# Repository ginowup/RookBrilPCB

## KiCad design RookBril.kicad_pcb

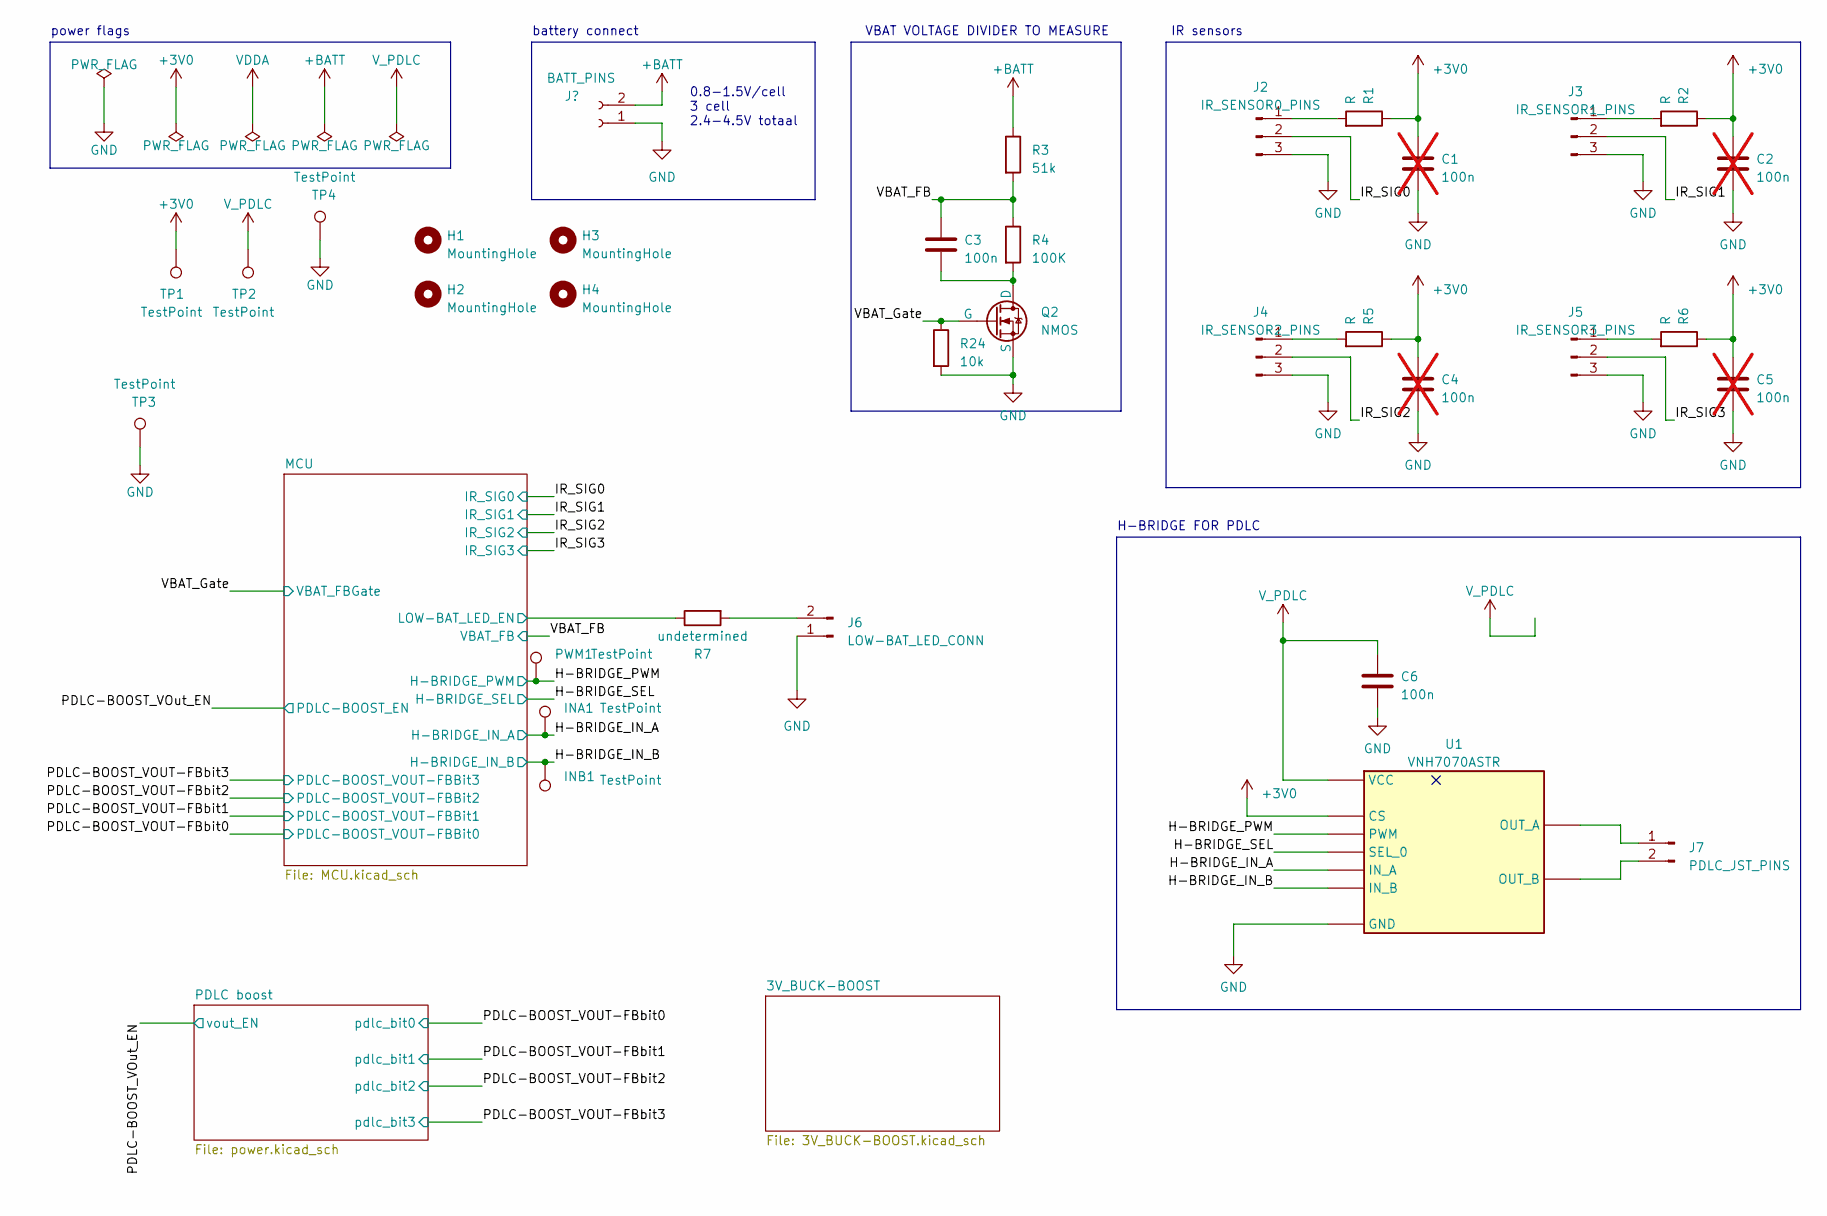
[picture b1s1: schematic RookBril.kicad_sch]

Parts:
C1, C2, C4, C5: 100n; C_0805_2012Metric_Pad1.18x1.45mm_HandSolder; not fitted
C3, C6: 100n; C_0805_2012Metric_Pad1.18x1.45mm_HandSolder
H1, H2, H3, H4: MountingHole; MountingHole_3mm
INA1: TestPoint; TestPoint_Pad_D1.0mm
INB1: TestPoint; TestPoint_Pad_D1.0mm
J1: BATT_PINS; PinHeader_1x02_P2.54mm_Vertical
J2: IR_SENSOR0_PINS; PinHeader_1x03_P2.54mm_Vertical
J3: IR_SENSOR1_PINS; PinHeader_1x03_P2.54mm_Vertical
J4: IR_SENSOR2_PINS; PinHeader_1x03_P2.54mm_Vertical
J5: IR_SENSOR3_PINS; PinHeader_1x03_P2.54mm_Vertical
J6: LOW-BAT_LED_CONN; PinHeader_1x02_P2.54mm_Vertical
J7: PDLC_JST_PINS; PinHeader_1x02_P2.54mm_Vertical
PWM1: TestPoint; TestPoint_Pad_D1.0mm
Q2: NMOS; SOT-23
R1, R2, R5, R6: R; R_0805_2012Metric_Pad1.20x1.40mm_HandSolder
R3: 51k; R_0805_2012Metric_Pad1.20x1.40mm_HandSolder
R4: 100K; R_0805_2012Metric_Pad1.20x1.40mm_HandSolder
R7: undetermined; R_0805_2012Metric_Pad1.20x1.40mm_HandSolder
R24: 10k; R_0805_2012Metric_Pad1.20x1.40mm_HandSolder
TP1, TP2, TP4: TestPoint; TestPoint_Plated_Hole_D2.0mm
TP3: TestPoint; exposedPad5x10
U1: VNH7070ASTR; SOIC127P600X175-16N; Manufacturer_Part_Number VNH7070ASTR; Mouser Part Number 511-VNH7070ASTR

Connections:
+3V0: C1.1, C2.1, C4.1, C5.1, R1.1, R2.1, R5.1, R6.1, TP1.1, U1.13 (CS); also elsewhere on the board
+BATT: J1.2, R3.1; also elsewhere on the board
/H-BRIDGE_IN_A: INA1.1, U1.3 (IN_A); also elsewhere on the board
/H-BRIDGE_IN_B: INB1.1, U1.6 (IN_B); also elsewhere on the board
/H-BRIDGE_PWM: PWM1.1, U1.11 (PWM); also elsewhere on the board
/H-BRIDGE_SEL: U1.14 (SEL_0); also elsewhere on the board
/IR_SIG0: J2.2; also elsewhere on the board
/IR_SIG1: J3.2; also elsewhere on the board
/IR_SIG2: J4.2; also elsewhere on the board
/IR_SIG3: J5.2; also elsewhere on the board
/MCU/LOW-BAT_LED_EN: R7.1; also elsewhere on the board
/VBAT_FB: C3.1, R3.2, R4.1; also elsewhere on the board
GND: C1.2, C2.2, C4.2, C5.2, C6.2, J1.1, J2.3, J3.3, J4.3, J5.3, J6.1, Q2.3 (S), R24.2, TP3.1, TP4.1, U1.1 (GND), U1.8 (GND), U1.9 (GND), U1.16 (GND); also elsewhere on the board
unnamed: J2.1, R1.2
unnamed: J3.1, R2.2
unnamed: J4.1, R5.2
unnamed: J5.1, R6.2
unnamed: J6.2, R7.2
unnamed: J7.1, U1.2 (OUT_A), U1.15 (OUT_A)
unnamed: J7.2, U1.7 (OUT_B), U1.10 (OUT_B)
VCC: C6.1, TP2.1, U1.4 (VCC), U1.5 (VCC), U1.12 (VCC); also elsewhere on the board

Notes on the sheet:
0.8-1.5V/cell 3 cell 2.4-4.5V totaal
VBAT VOLTAGE DIVIDER TO MEASURE
battery connect
IR sensors
H-BRIDGE FOR PDLC
power flags

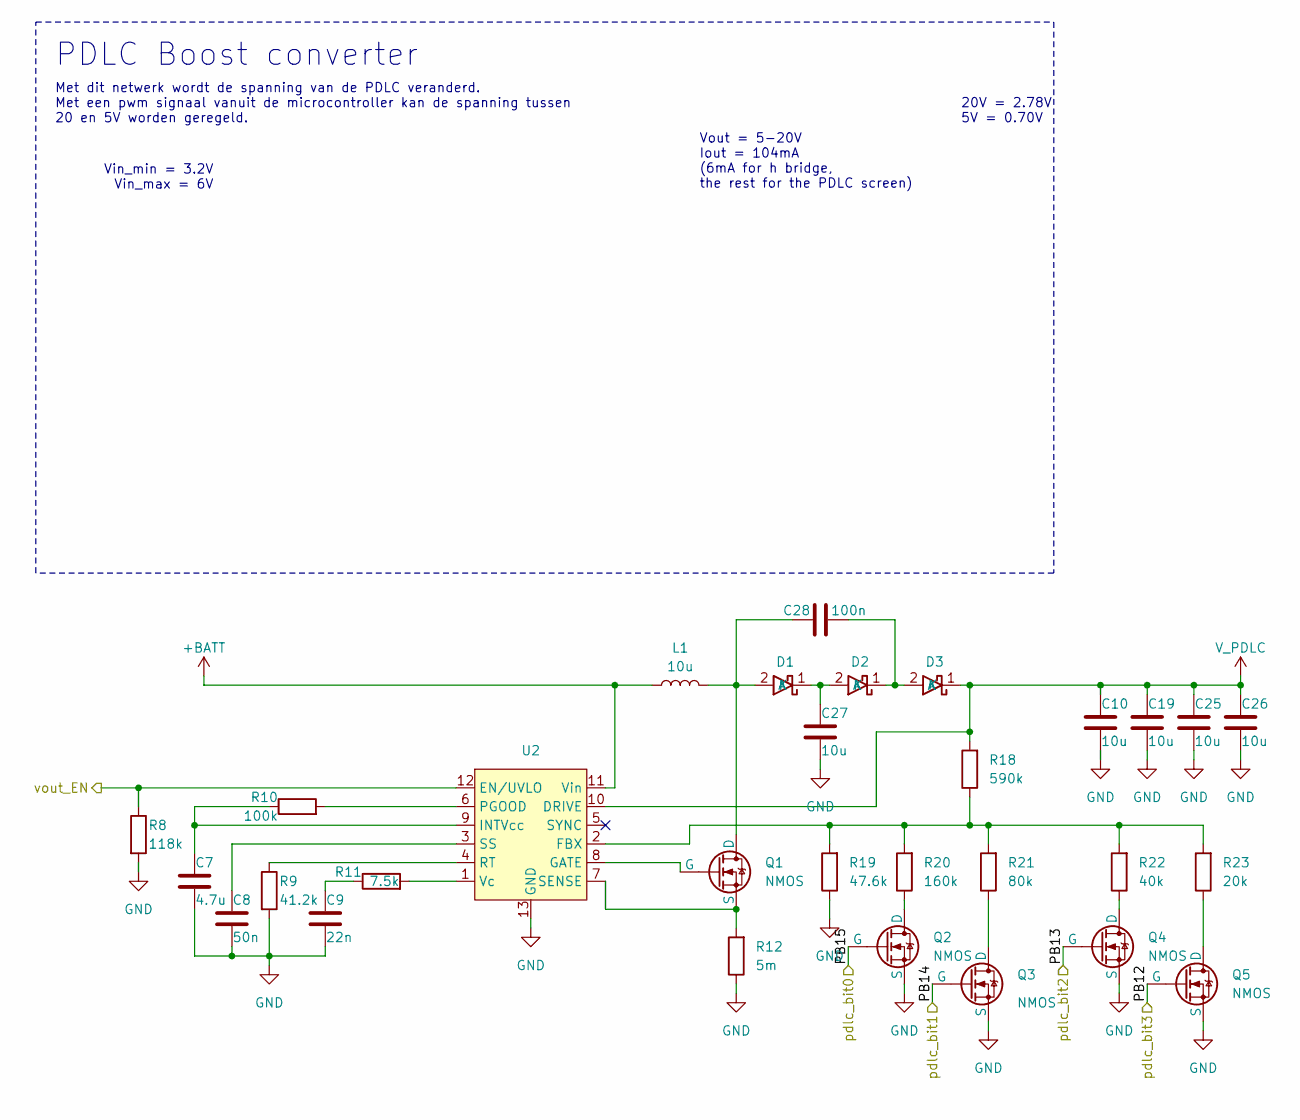
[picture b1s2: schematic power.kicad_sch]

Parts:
C7: 4.7u; C_0805_2012Metric_Pad1.18x1.45mm_HandSolder
C8: 50n; C_0805_2012Metric_Pad1.18x1.45mm_HandSolder
C9: 22n; C_0805_2012Metric_Pad1.18x1.45mm_HandSolder
C10, C19, C25, C26, C27: 10u; C_0805_2012Metric_Pad1.18x1.45mm_HandSolder
C28: 100n; C_0805_2012Metric_Pad1.18x1.45mm_HandSolder
D1, D2, D3: D_SOD-123F
L1: 10u; MRS8030T100
Q1, Q2, Q3, Q4, Q5: NMOS; SOT-23
R8: 118k; R_0805_2012Metric_Pad1.20x1.40mm_HandSolder
R9: 41.2k; R_0805_2012Metric_Pad1.20x1.40mm_HandSolder
R10: 100k; R_0805_2012Metric_Pad1.20x1.40mm_HandSolder
R11: 7.5k; R_0805_2012Metric_Pad1.20x1.40mm_HandSolder
R12: 5m; R_2010_5025Metric_Pad1.40x2.65mm_HandSolder
R18: 590k; R_0805_2012Metric_Pad1.20x1.40mm_HandSolder
R19: 47.6k; R_0805_2012Metric_Pad1.20x1.40mm_HandSolder
R20: 160k; R_0805_2012Metric_Pad1.20x1.40mm_HandSolder
R21: 80k; R_0805_2012Metric_Pad1.20x1.40mm_HandSolder
R22: 40k; R_0805_2012Metric_Pad1.20x1.40mm_HandSolder
R23: 20k; R_0805_2012Metric_Pad1.20x1.40mm_HandSolder
U2: LT3759

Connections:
+BATT: L1.1, U2.11 (Vin); also elsewhere on the board
/PDLC-BOOST_VOUT-FBbit1: Q3.2 (G); also elsewhere on the board
/PDLC-BOOST_VOUT-FBbit2: Q4.2 (G); also elsewhere on the board
/PDLC-BOOST_VOUT-FBbit3: Q5.2 (G); also elsewhere on the board
/PDLC-BOOST_VOut_EN: R8.1, U2.12 (EN/UVLO); also elsewhere on the board
GND: C7.1, C8.1, C9.1, C10.1, C19.1, C25.1, C26.1, C27.1, Q2.3 (S), Q3.3 (S), Q4.3 (S), Q5.3 (S), R8.2, R9.2, R12.1, R19.1, U2.13 (GND); also elsewhere on the board
unnamed: C9.2, R11.1
unnamed: C28.2, D1.2 (A), L1.2, Q1.1 (D)
unnamed: C27.2, D1.1 (K), D2.2 (A)
unnamed: C28.1, D2.1 (K), D3.2 (A)
unnamed: Q1.2 (G), U2.8 (GATE)
unnamed: Q1.3 (S), R12.2, U2.7 (SENSE)
unnamed: Q3.1 (D), R21.1
unnamed: Q4.1 (D), R22.1
unnamed: Q5.1 (D), R23.1
unnamed: R18.1, R19.2, R20.2, R21.2, R22.2, R23.2, U2.2 (FBX)
unnamed: C7.2, R10.1, U2.9 (INTVcc)
unnamed: R10.2, U2.6 (PGOOD)
unnamed: R9.1, U2.4 (RT)
unnamed: C8.2, U2.3 (SS)
unnamed: R11.2, U2.1 (Vc)
VCC: C10.2, C19.2, C25.2, C26.2, D3.1 (K), R18.2, U2.10 (DRIVE); also elsewhere on the board

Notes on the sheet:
Vout = 5-20V Iout = 104mA (6mA for h bridge, the rest for the PDLC screen)
Vin_min = 3.2V Vin_max = 6V
20V = 2.78V 5V = 0.70V
PDLC Boost converter
Met dit netwerk wordt de spanning van de PDLC veranderd. Met een pwm signaal vanuit de microcontroller kan de spanning tussen 20 en 5V worden geregeld.

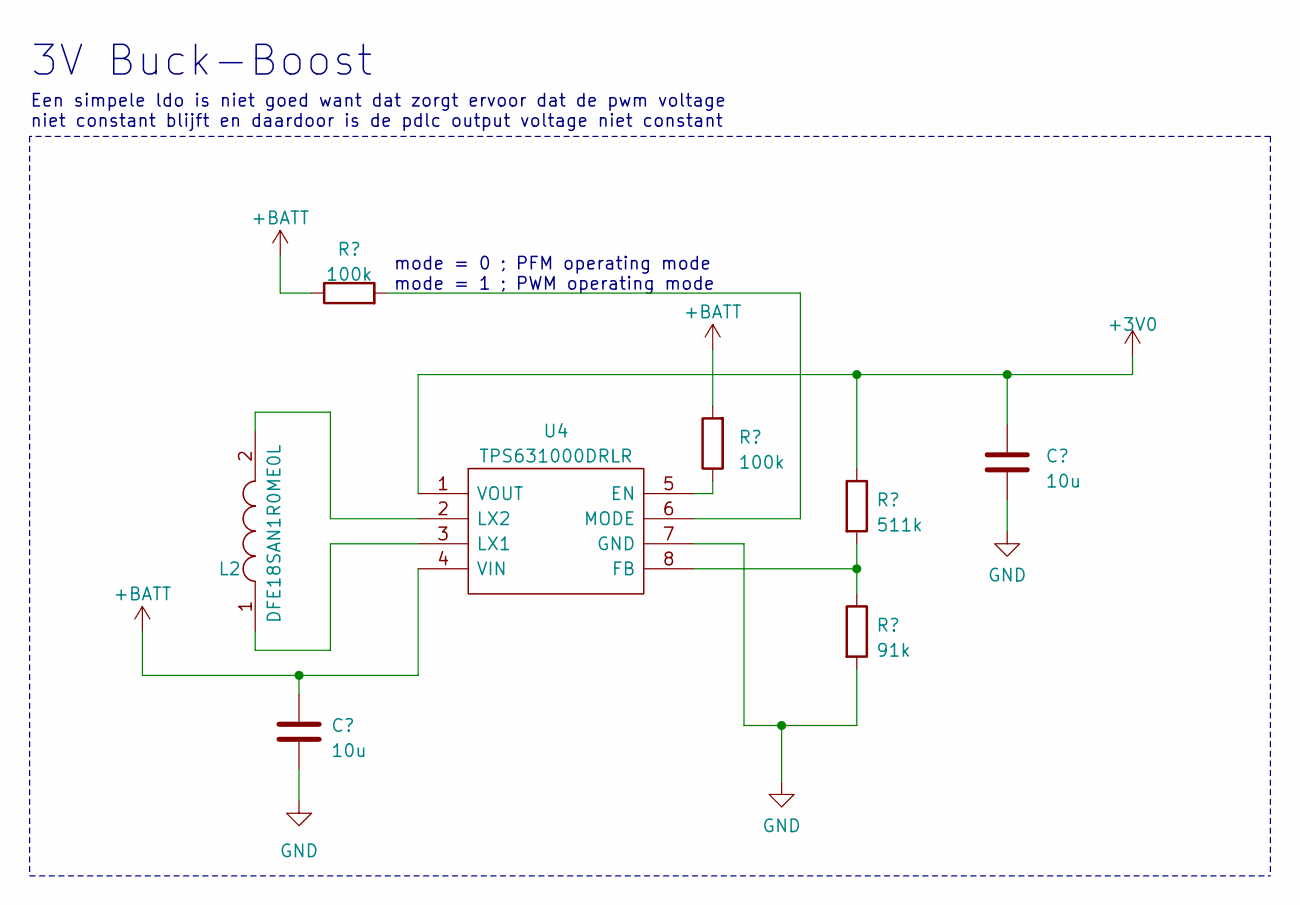
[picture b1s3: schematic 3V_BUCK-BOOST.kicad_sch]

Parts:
C22, C23: 10u; C_0805_2012Metric_Pad1.18x1.45mm_HandSolder
L2: DFE18SAN1R0ME0L; Mouser Part Number 81-DFE18SAN1R0ME0L
R14, R15: 100k; R_0805_2012Metric_Pad1.20x1.40mm_HandSolder
R16: 511k; R_0805_2012Metric_Pad1.20x1.40mm_HandSolder
R17: 91k; R_0805_2012Metric_Pad1.20x1.40mm_HandSolder
U4: TPS631000DRLR; SOTFL50P160X60-8N; Mouser Part Number 595-TPS631000DRLR

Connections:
+3V0: C22.1, R16.1, U4.1 (VOUT); also elsewhere on the board
+BATT: C23.1, R14.1, R15.2, U4.4 (VIN); also elsewhere on the board
GND: C22.2, C23.2, R17.2, U4.7 (GND); also elsewhere on the board
unnamed: R15.1, U4.5 (EN)
unnamed: R16.2, R17.1, U4.8 (FB)
unnamed: L2.1, U4.3 (LX1)
unnamed: L2.2, U4.2 (LX2)
unnamed: R14.2, U4.6 (MODE)

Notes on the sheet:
3V Buck-Boost
Een simpele ldo is niet goed want dat zorgt ervoor dat de pwm voltage niet constant blijft en daardoor is de pdlc output voltage niet constant
mode = 0 ; PFM operating mode mode = 1 ; PWM operating mode

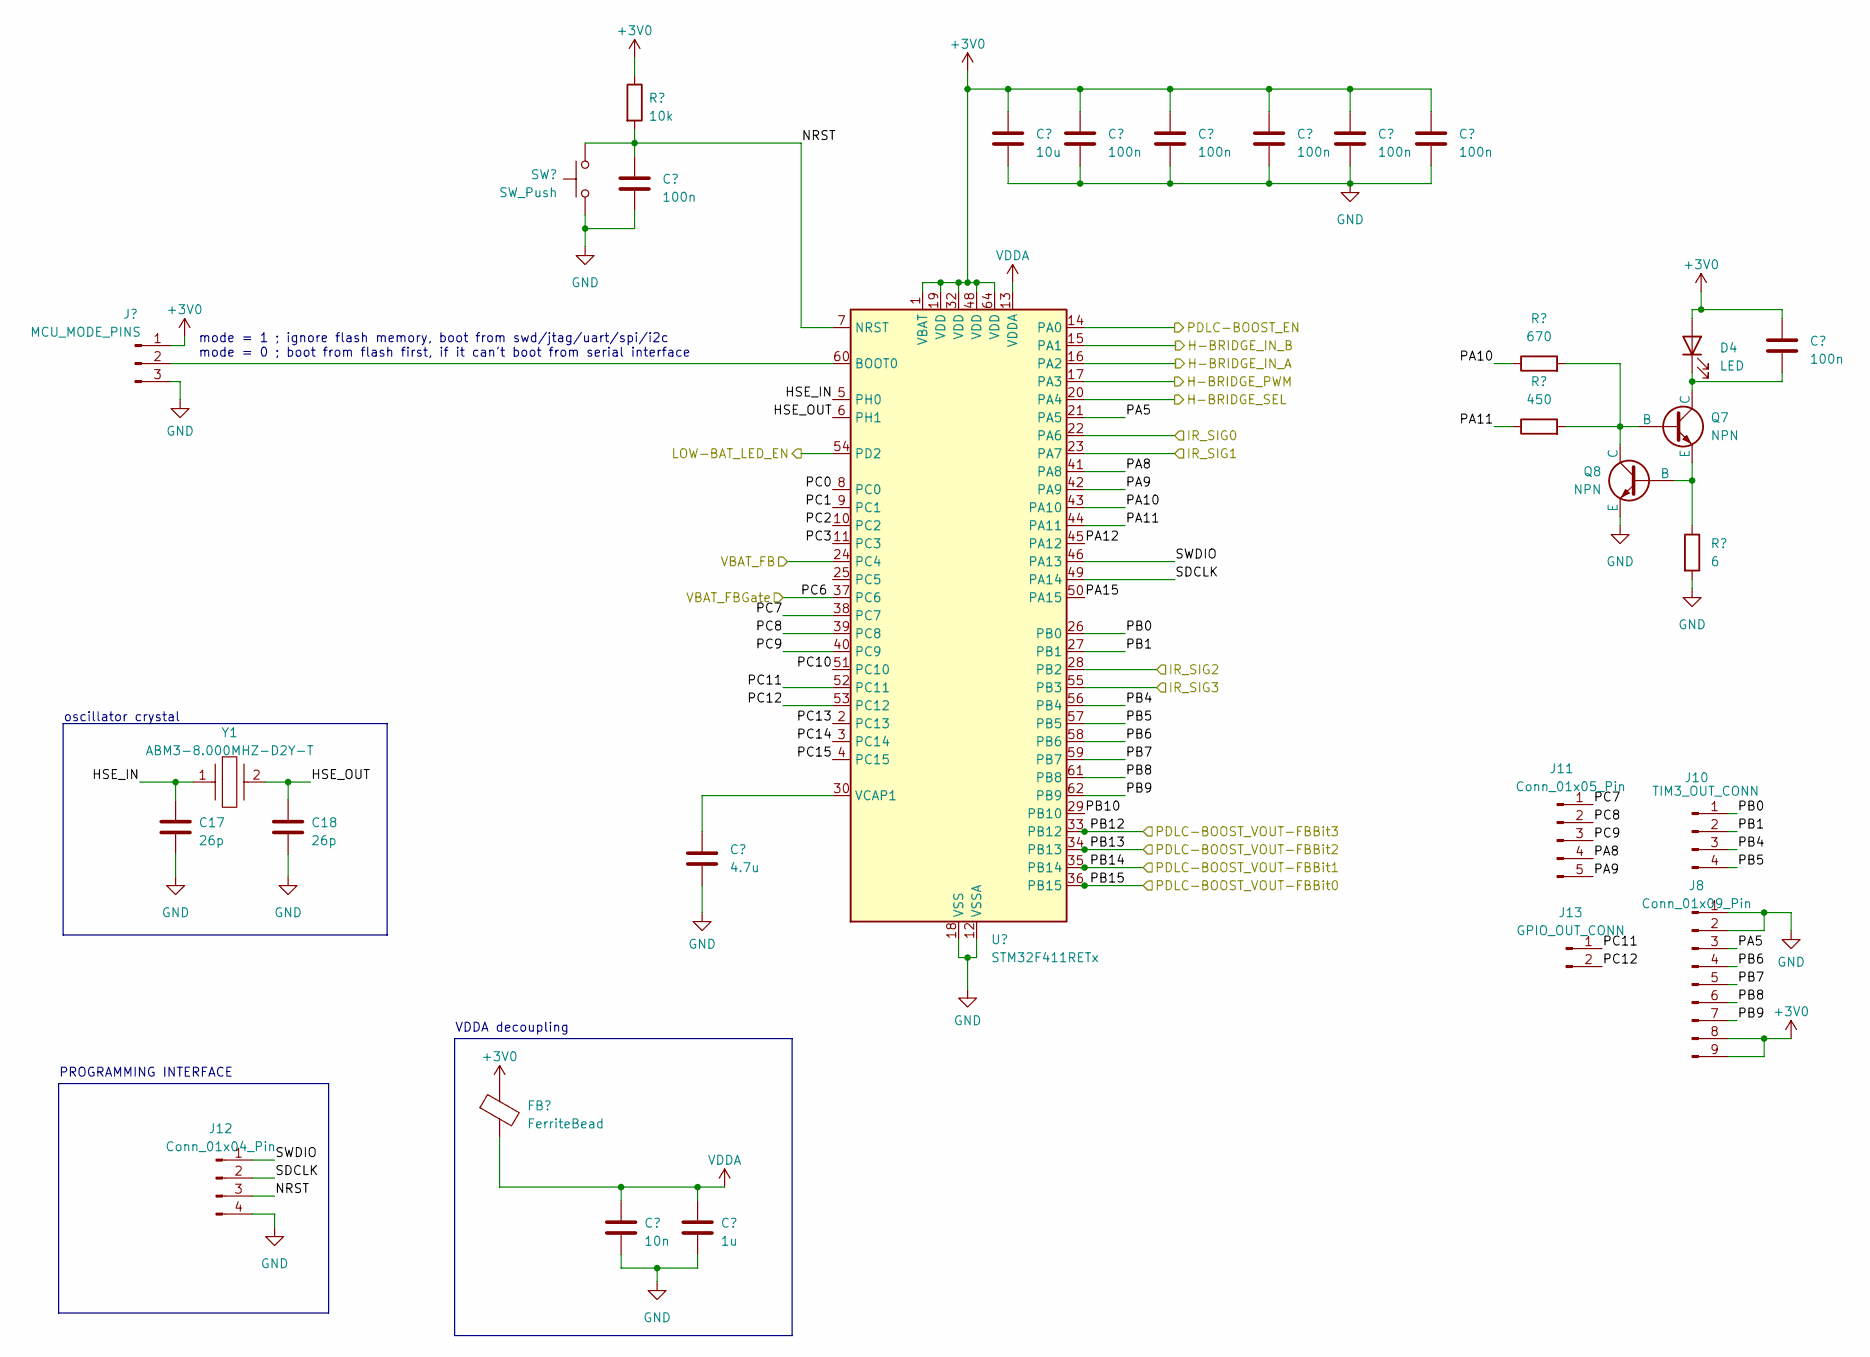
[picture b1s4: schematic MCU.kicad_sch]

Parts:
C11: 10u; C_0805_2012Metric_Pad1.18x1.45mm_HandSolder
C12, C13, C14, C15, C16, C24, C30: 100n; C_0805_2012Metric_Pad1.18x1.45mm_HandSolder
C17, C18: 26p; C_0805_2012Metric_Pad1.18x1.45mm_HandSolder
C20: 10n; C_0805_2012Metric_Pad1.18x1.45mm_HandSolder
C21: 1u; C_0805_2012Metric_Pad1.18x1.45mm_HandSolder
C29: 4.7u; C_0805_2012Metric_Pad1.18x1.45mm_HandSolder
D4: LED; IRLED
FB1: FerriteBead; L_0805_2012Metric_Pad1.15x1.40mm_HandSolder
J8: Conn_01x09_Pin; PinHeader_1x09_P2.54mm_Vertical
J9: MCU_MODE_PINS; PinHeader_1x03_P2.54mm_Vertical
J10: TIM3_OUT_CONN; PinHeader_1x04_P2.54mm_Vertical
J11: Conn_01x05_Pin; PinHeader_1x05_P2.54mm_Vertical
J12: Conn_01x04_Pin; PinHeader_1x04_P2.54mm_Vertical
J13: GPIO_OUT_CONN; PinHeader_1x02_P2.54mm_Vertical
Q7, Q8: NPN; SOT-23
R13: 10k; R_0805_2012Metric_Pad1.20x1.40mm_HandSolder
R25: 6; R_0805_2012Metric_Pad1.20x1.40mm_HandSolder
R26: 450; R_0805_2012Metric_Pad1.20x1.40mm_HandSolder
R27: 670; R_0805_2012Metric_Pad1.20x1.40mm_HandSolder
SW1: SW_Push; SW_PUSH_6mm_H5mm
U3: STM32F411RETx; LQFP-64_10x10mm_P0.5mm
Y1: ABM3-8.000MHZ-D2Y-T; ABM3; Mouser Part Number 815-ABM3-8-D2Y-T

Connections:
+3V0: C11.1, C12.1, C13.1, C14.1, C15.1, C24.1, C30.1, D4.2 (A), FB1.1, J8.8, J8.9, J9.1, R13.1, U3.1 (VBAT), U3.19 (VDD), U3.32 (VDD), U3.48 (VDD), U3.64 (VDD); also elsewhere on the board
/H-BRIDGE_IN_A: U3.16 (PA2); also elsewhere on the board
/H-BRIDGE_IN_B: U3.15 (PA1); also elsewhere on the board
/H-BRIDGE_PWM: U3.17 (PA3); also elsewhere on the board
/H-BRIDGE_SEL: U3.20 (PA4); also elsewhere on the board
/IR_SIG0: U3.22 (PA6); also elsewhere on the board
/IR_SIG1: U3.23 (PA7); also elsewhere on the board
/IR_SIG2: U3.28 (PB2); also elsewhere on the board
/IR_SIG3: U3.55 (PB3); also elsewhere on the board
/MCU/HSE_IN: C17.1, U3.5 (PH0), Y1.1
/MCU/HSE_OUT: C18.1, U3.6 (PH1), Y1.2
/MCU/LOW-BAT_LED_EN: U3.54 (PD2); also elsewhere on the board
/MCU/NRST: C16.1, J12.3, R13.2, SW1.1, U3.7 (NRST)
/MCU/PA5: J8.3, U3.21 (PA5)
/MCU/PA8: J11.4, U3.41 (PA8)
/MCU/PA9: J11.5, U3.42 (PA9)
/MCU/PA10: R27.1, U3.43 (PA10)
/MCU/PA11: R26.1, U3.44 (PA11)
/MCU/PA12: U3.45 (PA12)
/MCU/PA15: U3.50 (PA15)
/MCU/PB0: J10.1, U3.26 (PB0)
/MCU/PB1: J10.2, U3.27 (PB1)
/MCU/PB4: J10.3, U3.56 (PB4)
/MCU/PB5: J10.4, U3.57 (PB5)
/MCU/PB6: J8.4, U3.58 (PB6)
/MCU/PB7: J8.5, U3.59 (PB7)
/MCU/PB8: J8.6, U3.61 (PB8)
/MCU/PB9: J8.7, U3.62 (PB9)
/MCU/PB10: U3.29 (PB10)
/MCU/PC0: U3.8 (PC0)
/MCU/PC1: U3.9 (PC1)
/MCU/PC2: U3.10 (PC2)
/MCU/PC3: U3.11 (PC3)
/MCU/PC7: J11.1, U3.38 (PC7)
/MCU/PC8: J11.2, U3.39 (PC8)
/MCU/PC9: J11.3, U3.40 (PC9)
/MCU/PC10: U3.51 (PC10)
/MCU/PC11: J13.1, U3.52 (PC11)
/MCU/PC12: J13.2, U3.53 (PC12)
/MCU/PC13: U3.2 (PC13)
/MCU/PC14: U3.3 (PC14)
/MCU/PC15: U3.4 (PC15)
/MCU/SDCLK: J12.2, U3.49 (PA14)
/MCU/SWDIO: J12.1, U3.46 (PA13)
/PDLC-BOOST_VOUT-FBbit1: U3.35 (PB14); also elsewhere on the board
/PDLC-BOOST_VOUT-FBbit2: U3.34 (PB13); also elsewhere on the board
/PDLC-BOOST_VOUT-FBbit3: U3.33 (PB12); also elsewhere on the board
/PDLC-BOOST_VOut_EN: U3.14 (PA0); also elsewhere on the board
/VBAT_FB: U3.24 (PC4); also elsewhere on the board
GND: C11.2, C12.2, C13.2, C14.2, C15.2, C16.2, C17.2, C18.2, C20.2, C21.2, C24.2, C29.2, J8.1, J8.2, J9.3, J12.4, Q8.3 (E), R25.2, SW1.2, U3.12 (VSSA), U3.18 (VSS), U3.31 (VSS), U3.47 (VSS), U3.63 (VSS); also elsewhere on the board
unnamed: C30.2, D4.1 (K), Q7.1 (C)
unnamed: J9.2, U3.60 (BOOT0)
unnamed: Q7.2 (B), Q8.1 (C), R26.2, R27.2
unnamed: Q7.3 (E), Q8.2 (B), R25.1
unnamed: C29.1, U3.30 (VCAP1)
VDDA: C20.1, C21.1, FB1.2, U3.13 (VDDA)

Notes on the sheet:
VDDA decoupling
PROGRAMMING INTERFACE
oscillator crystal
mode = 1 ; ignore flash memory, boot from swd/jtag/uart/spi/i2c mode = 0 ; boot from flash first, if it can't boot from serial interface

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
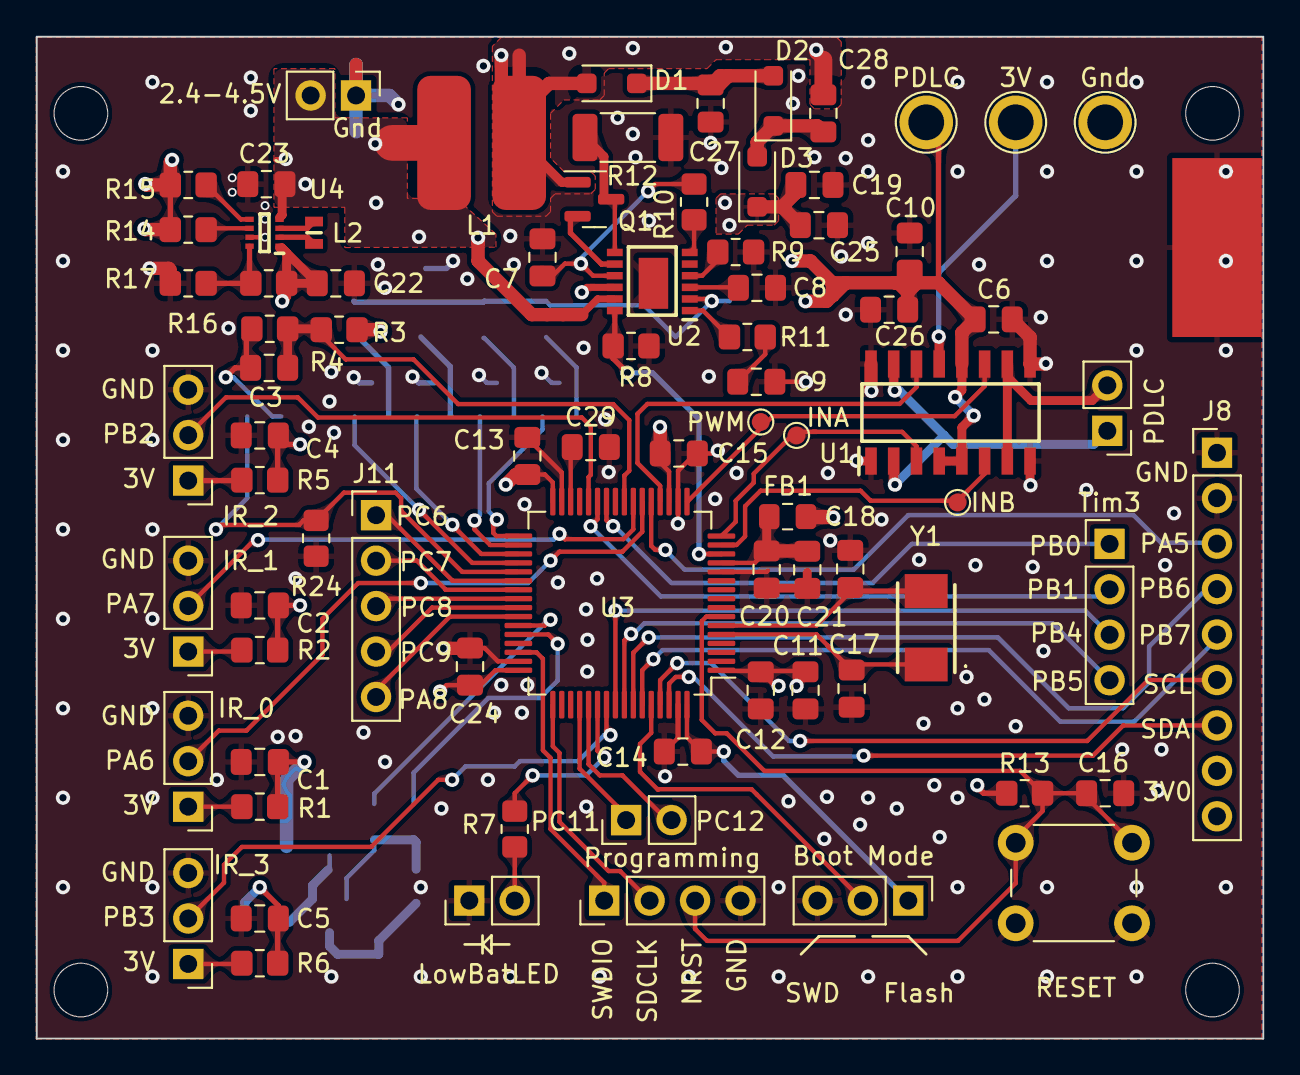
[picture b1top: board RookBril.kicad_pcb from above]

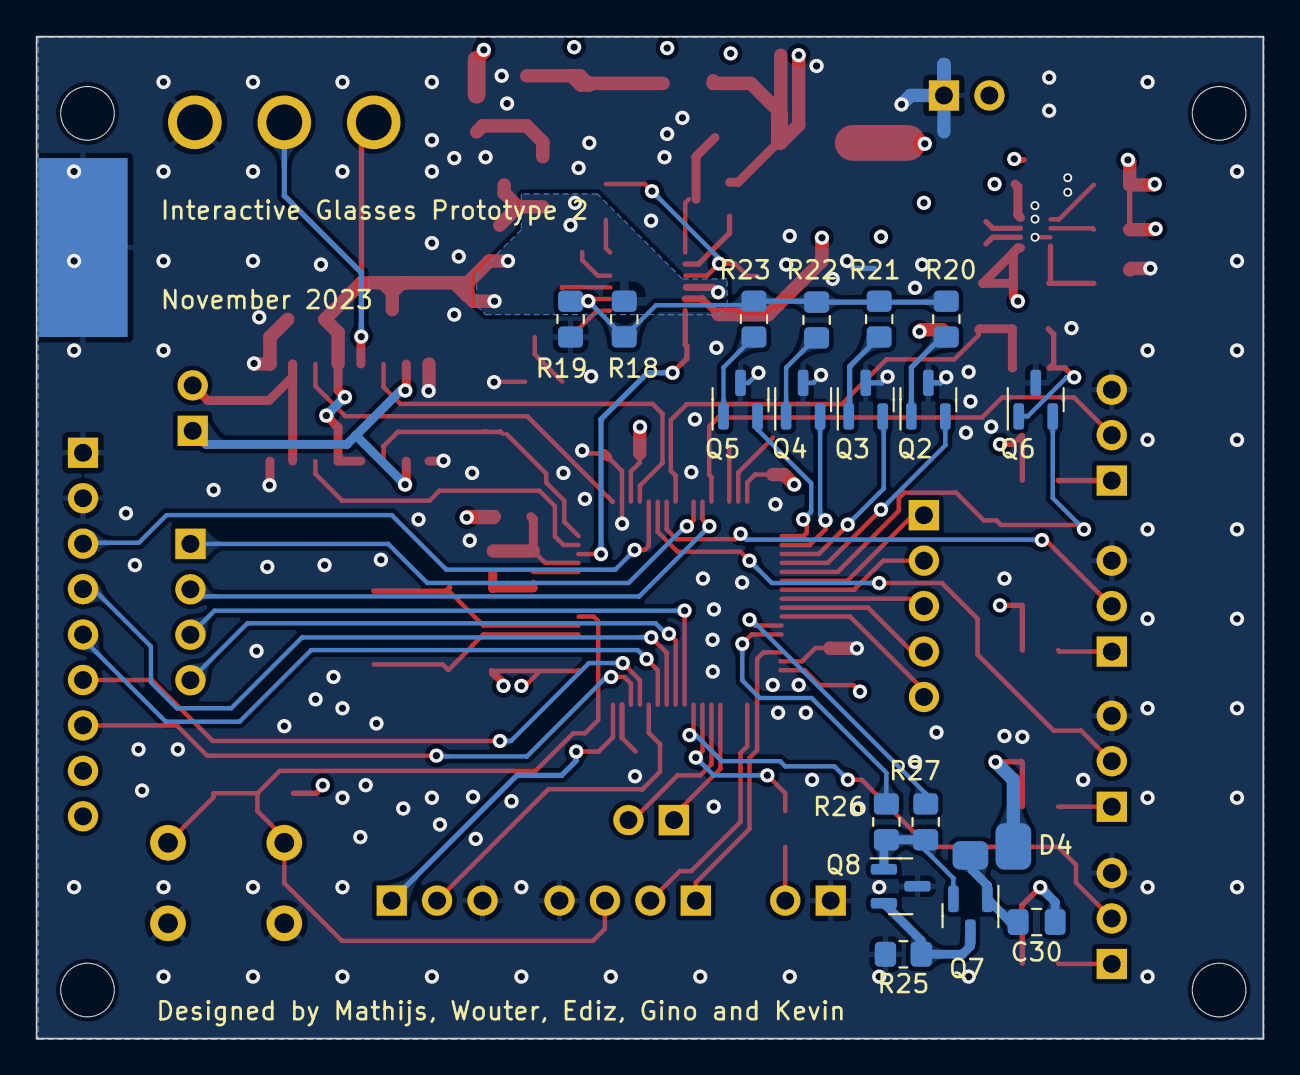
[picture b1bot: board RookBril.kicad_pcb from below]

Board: 4 copper layers, 68.6 x 56.0 mm, 102 parts (18 on the bottom side), 78 nets.

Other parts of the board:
Q6: NMOS; SOT-23

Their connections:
GND: Q6.3 (S); also elsewhere on the board

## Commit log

2023-10-11 Started Project, added PDLC and the boost ic
2023-10-12 Buffed the diode, changed compensation components
2023-10-12 updated schematic
    alles toegevoegd aan de schematic
2023-10-13 footprint assignments gedaan + verbeteringen
2023-10-13 aantal componenten veranderd.
2023-10-13 beginsel aan pcb gemaakt
2023-10-16 Alle verbindingen gelegt van de componenten.
    Moet nog bij nog tekst bij de connectoren zetten. Ook zijn de unconnected pinnen weggehaald, omdat het onmogelijk maakt voor een 2 laags PCB.
2023-10-17 nieuwe layout
2023-10-17 betere
2023-10-18 bijna alle verbindingen gelegd
2023-10-18 Alles klaar 1 error, en nog silkscreen fixen
2023-10-20 Klein beetje reorganiseren van de lay-out Silkscreen schoongemaakt TestPoints en Mounting holes toegevoegd
2023-10-20 Kleine veranderingen gebaseerd op feedback whatsapp
2023-10-20 updated schematic en interactive bom in de git
2023-10-20 new pad, and made ibom
2023-10-20 Production files for JLC with the addon
2023-11-03 kleine dingen
2023-11-26 NieuwePDLCVoedingen
    -LT1308
    -LT3759
    -Mixed schematic
    -Mixed footprints
2023-11-27 PCBv2.01
    Eerste versie van de tweede versie van de pcb prototype.
    Nieuwe PDLC voeding, extra pinnen beschikbaar voor GUI inclusief voeding pinnen.
2023-11-28 PCBv2.02
    Toepassingen van wouters feedback.
    Condensatoren beter geplaatst bij pdlc, mosfet toegevoegd bij fb bat, extra vias toegevoegd en traces verschoven voor betere GND plane connecties
2023-11-28 VierLaagsVersie
    Snel in elkaar gegooide vier laags pcb, Deze zou veel betere GND en voeding paden hebben.
    Als we tijd hebben/hadden kon deze nog beter worden gemaakt door alle traces te rerouten, er zullen veel traces door minder vias kunnen nu maar dit zal werken as is.
2023-11-28 PCB4Lv0.1
    (vergat goed te saven)
2023-11-28 PCB4Lv0.2
    Paar dingen nog extra vergeten, IR LED toegevoegd aan de bottom side.
2023-11-28 Paar kleine veranderingen, ziet er mooi uit
2023-11-30 Ordered this one
